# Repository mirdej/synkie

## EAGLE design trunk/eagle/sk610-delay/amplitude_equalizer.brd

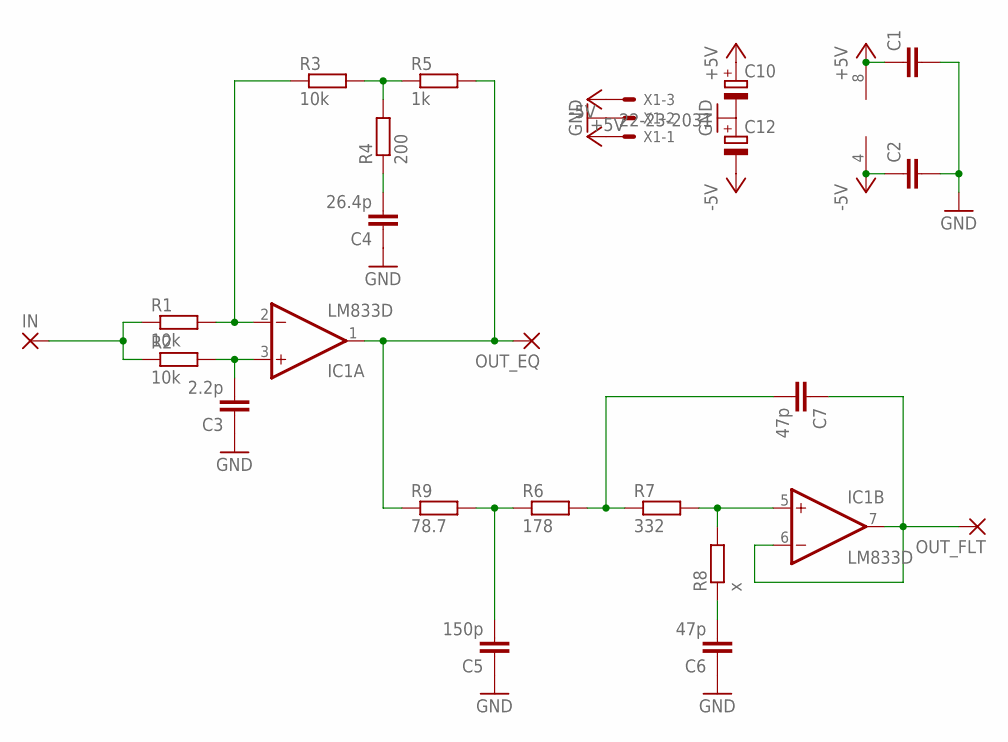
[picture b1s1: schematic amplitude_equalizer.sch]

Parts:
C1, C2: C-EUC1206; C1206
C3: 2.2p; C1206
C4: 26.4p; C1206
C5: 150p; C1206
C6, C7: 47p; C1206
C10, C12: CPOL-EUCT6032; CT6032
IC1: LM833D; SO08
IN: 3,17/1,1
OUT_EQ: 3,17/1,1
OUT_FLT: 3,17/1,1
R1, R2, R3: 10k; R1206
R4: 200; R1206
R5: 1k; R1206
R6: 178; R1206
R7: 332; R1206
R8: x; R1206
R9: 78.7; R1206
X1: 22-23-2031

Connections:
+5V: C1.1, C10.+, IC1.8 (V+), X1.3
-5V: C2.1, C12.-, IC1.4 (V-), X1.1
GND: C1.2, C2.2, C3.1, C4.1, C5.1, C6.1, C10.-, C12.+, X1.2
unnamed: IC1.2 (-IN), R1.2, R3.1
unnamed: C3.2, IC1.3 (+IN), R2.2
unnamed: IN.1, R1.1, R2.1
unnamed: IC1.1 (OUT), OUT_EQ.1, R5.2, R9.1
unnamed: C4.2, R4.1
unnamed: R3.2, R4.2, R5.1
unnamed: C5.2, R6.1, R9.2
unnamed: C7.2, R6.2, R7.1
unnamed: IC1.5 (+IN), R7.2, R8.2
unnamed: C6.2, R8.1
unnamed: C7.1, IC1.6 (-IN), IC1.7 (OUT), OUT_FLT.1

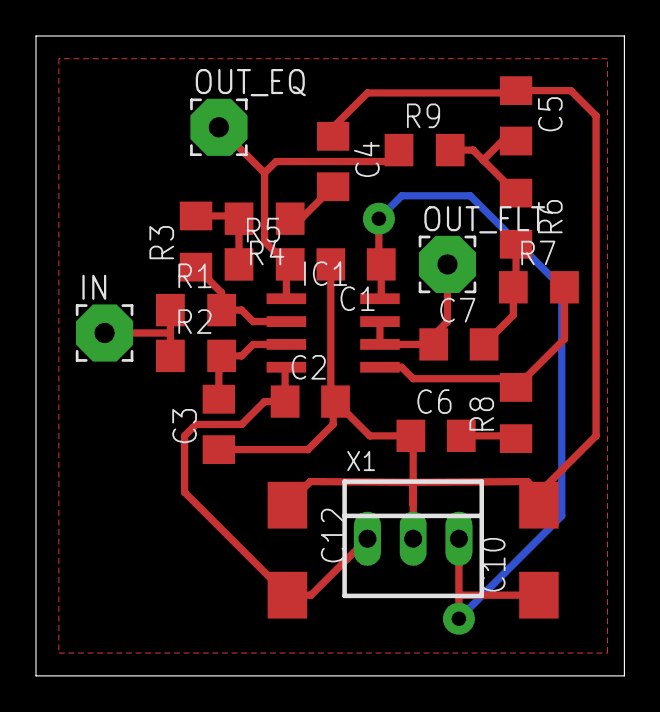
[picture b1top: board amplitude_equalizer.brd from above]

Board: 2 copper layers, 32.7 x 35.5 mm, 23 parts (0 on the bottom side), 14 nets.

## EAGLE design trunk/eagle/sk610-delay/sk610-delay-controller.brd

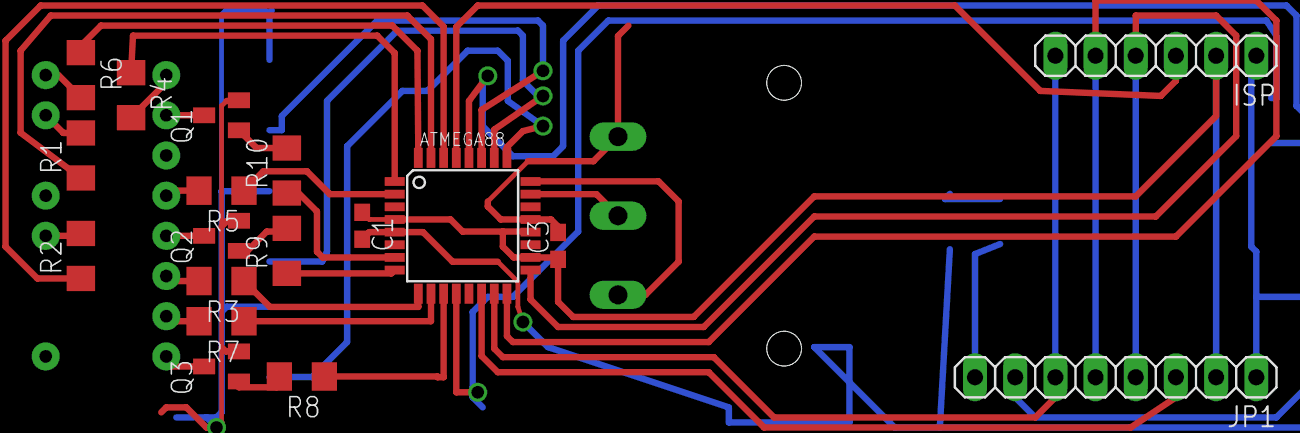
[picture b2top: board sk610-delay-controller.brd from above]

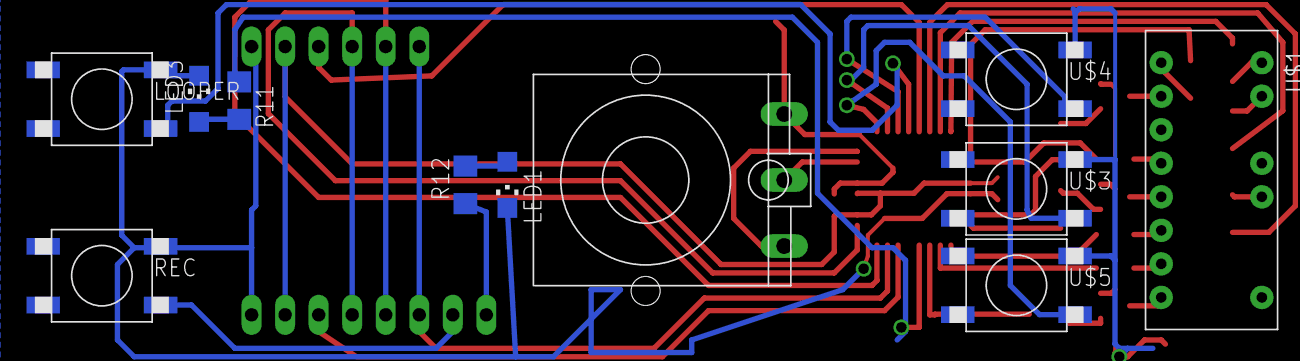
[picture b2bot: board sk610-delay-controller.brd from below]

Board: 2 copper layers, 29 parts (11 on the bottom side), 41 nets.

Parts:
ATMEGA88: ATMEGA88; TQFP32-08
C1, C3: C0603
ISP: 1X06
JP1: 1X08
LED1, LED3: CHIPLED_1206
LOOPER: PRINTTASTER_SMD; SMD_SWITCH
Q1, Q2, Q3: BC817-16LT1SMD; SOT23-BEC
R1, R2, R3, R4, R5, R6, R7, R8, R9, R10: R1206
R11, R12: 200; R1206
REC: PRINTTASTER_SMD; SMD_SWITCH
U$1: LTC-2721-7-SEGMENT; LTC-2721
U$2: STEC16B04
U$3, U$4, U$5: PRINTTASTER_SMD; SMD_SWITCH

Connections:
GND: ATMEGA88.5, ATMEGA88.21, C1.2, C3.2, ISP.1, JP1.1, LED1.C, LED3.C, LOOPER.AA, Q1.E, Q2.E, Q3.E, REC.AA, U$2.C, U$3.AA, U$4.AA, U$5.AA
unnamed: ATMEGA88.30, R2.1
unnamed: ATMEGA88.31, R1.1
unnamed: ATMEGA88.32, R6.1
unnamed: ATMEGA88.1, R4.1
unnamed: ATMEGA88.2, R5.1
unnamed: ATMEGA88.8, R9.1
unnamed: ATMEGA88.7, R10.1
unnamed: ATMEGA88.11, R8.1
unnamed: ATMEGA88.9, R3.1
unnamed: R1.2, U$1.P$12
unnamed: R2.2, U$1.P$10
unnamed: R3.2, U$1.P$6
unnamed: R4.2, U$1.P$1
unnamed: R5.2, U$1.P$4
unnamed: R6.2, U$1.P$13
unnamed: R7.2, U$1.P$7
unnamed: ATMEGA88.29, ISP.3
unnamed: ATMEGA88.17, ISP.4, JP1.4
unnamed: ATMEGA88.16, ISP.5, JP1.5
unnamed: ATMEGA88.15, ISP.6, JP1.6
unnamed: ATMEGA88.14, JP1.3
unnamed: ATMEGA88.10, R7.1
unnamed: ATMEGA88.23, U$2.B
unnamed: ATMEGA88.24, U$2.A
unnamed: Q1.B, R10.2
unnamed: Q2.B, R9.2
unnamed: Q3.B, R8.2
unnamed: Q1.C, U$1.P$2
unnamed: Q2.C, U$1.P$5
unnamed: Q3.C, U$1.P$8
unnamed: ATMEGA88.25, U$5.BB
unnamed: ATMEGA88.26, U$3.BB
unnamed: ATMEGA88.27, U$4.BB
unnamed: JP1.7, REC.BB
unnamed: ATMEGA88.28, LOOPER.BB
unnamed: ATMEGA88.12, R11.1
unnamed: LED1.A, R12.2
unnamed: JP1.8, R12.1
unnamed: LED3.A, R11.2
VCC: ATMEGA88.4, ATMEGA88.18, ATMEGA88.20, C1.1, C3.1, ISP.2, JP1.2

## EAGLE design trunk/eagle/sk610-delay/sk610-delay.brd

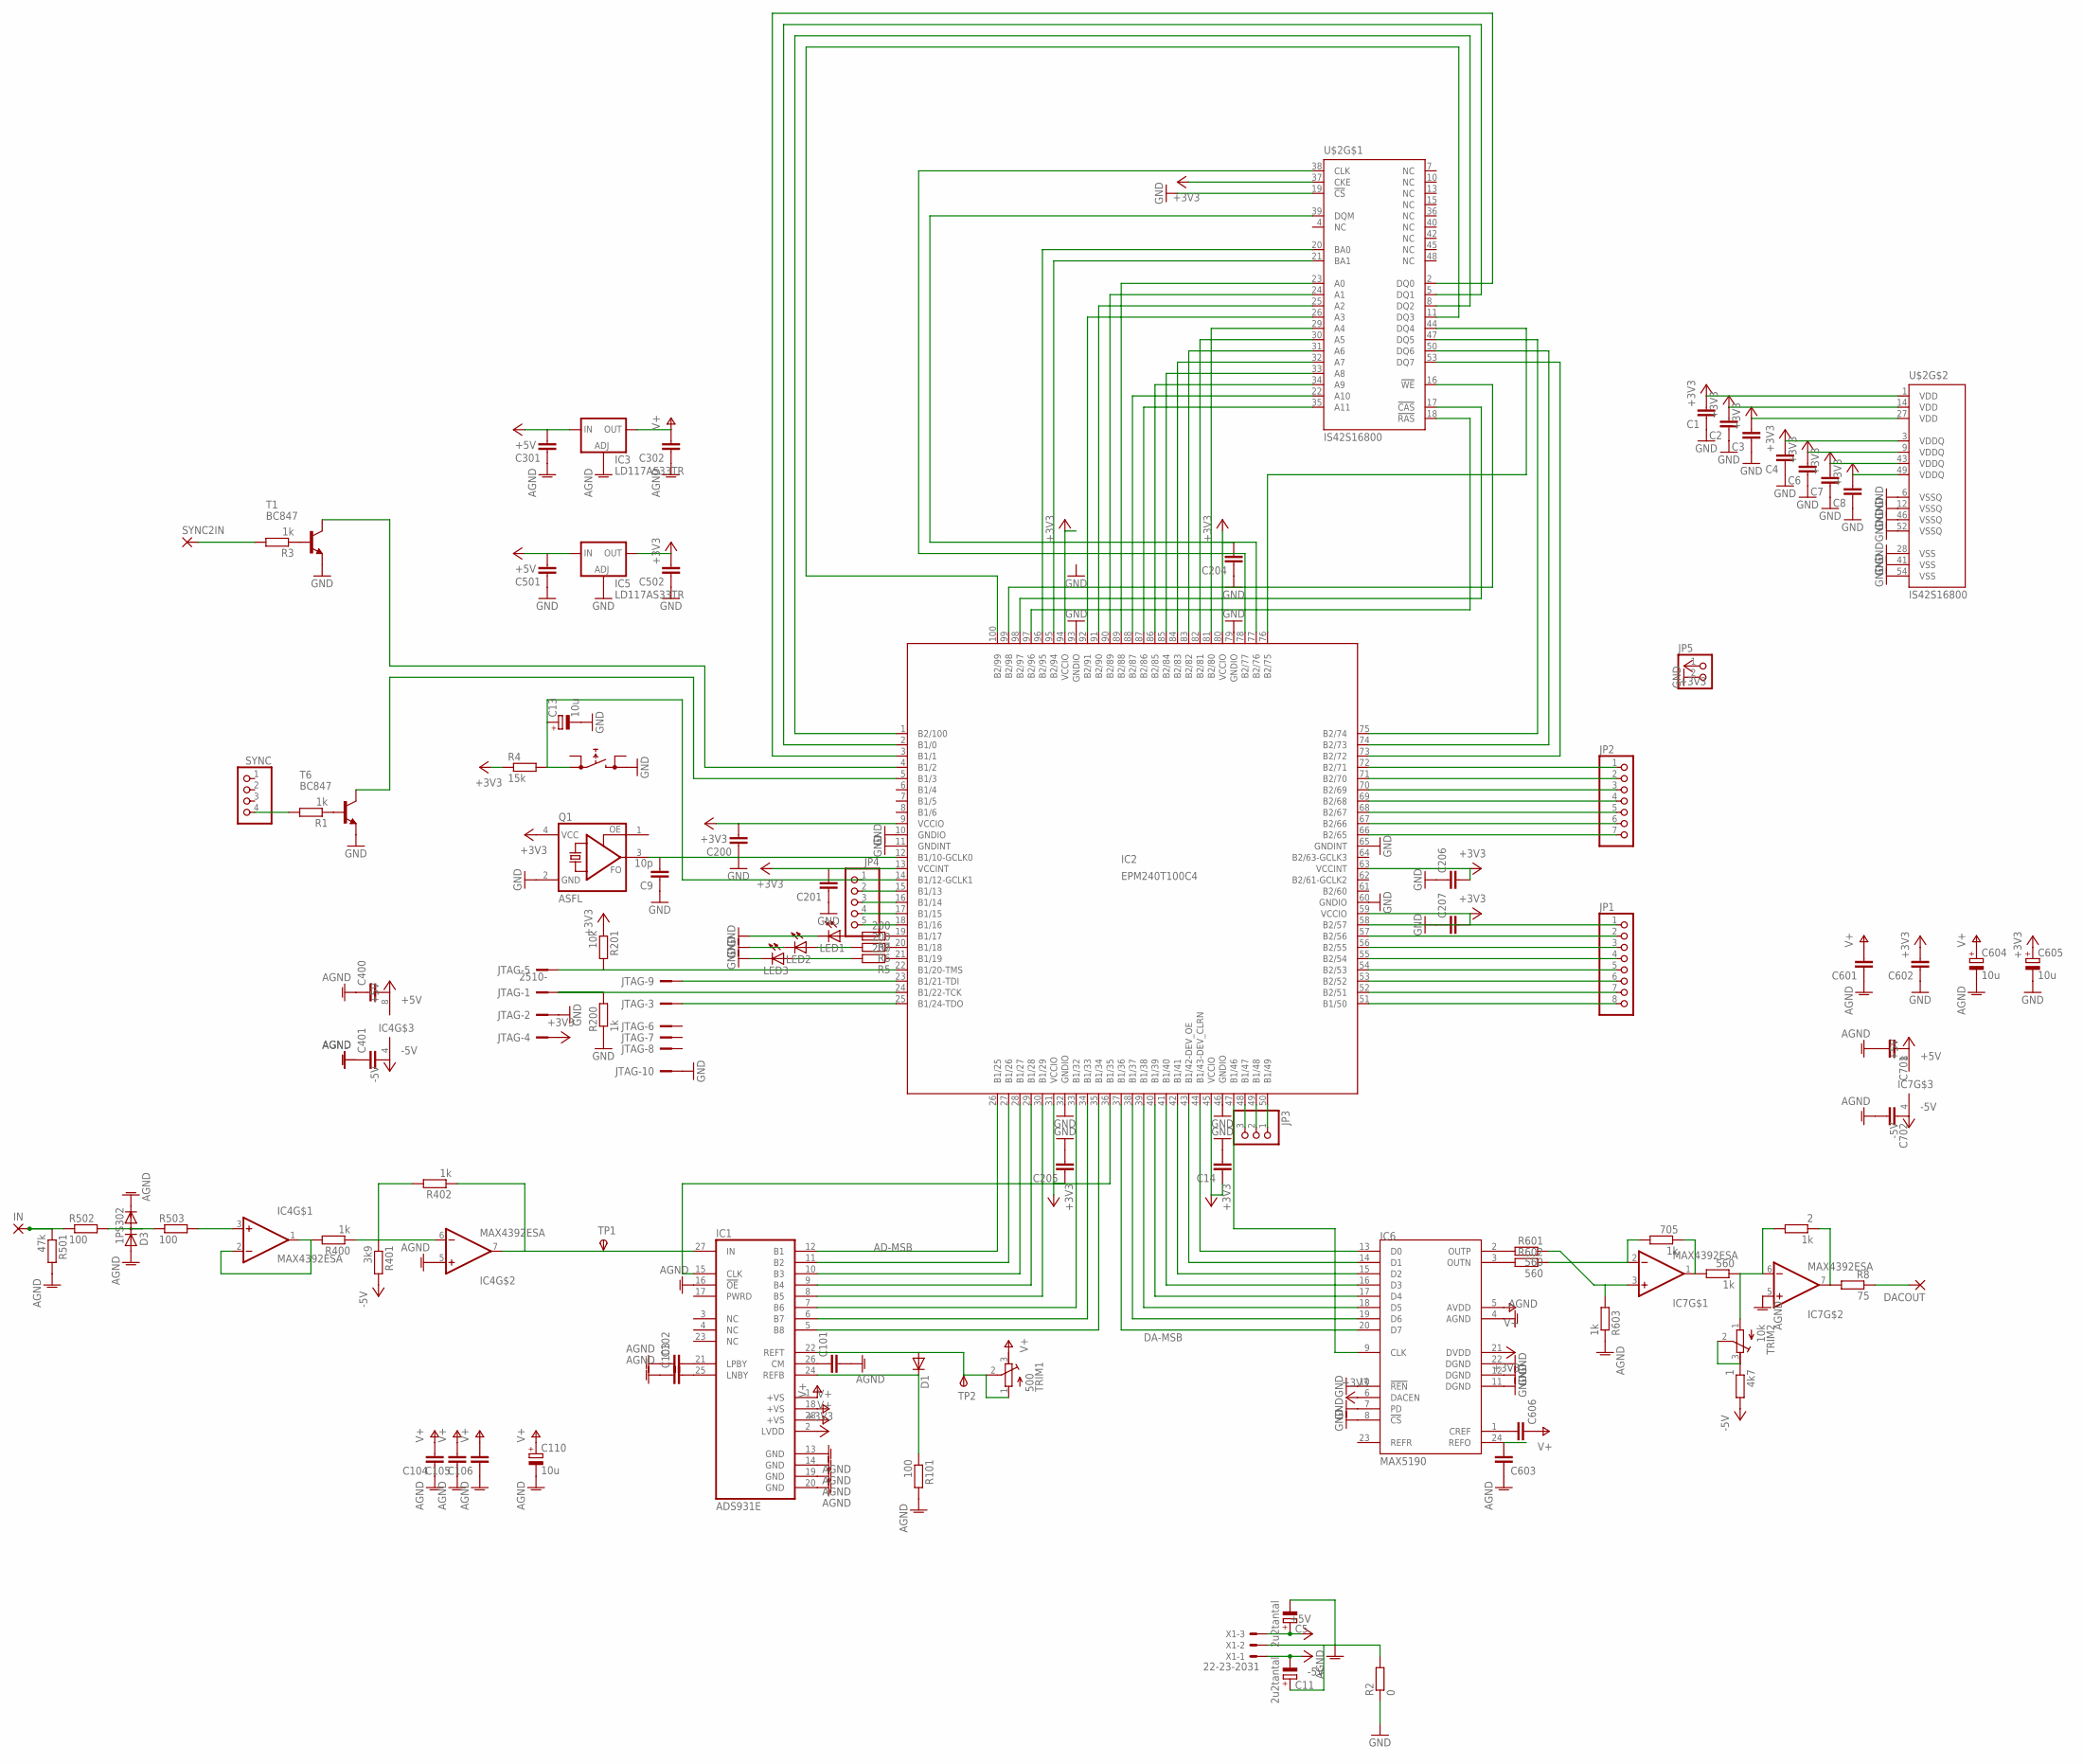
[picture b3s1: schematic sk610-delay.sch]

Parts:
1: 4k7; R1206
2, 560, 705: 1k; R1206
C1, C2, C3, C4, C6, C7, C8, C14, C101, C102, C103, C104, C106, C200, C201, C204, C205, C206, C207, C301, C302, C400, C401, C501, C502, C601, C602, C603, C606, C701, C702: C-EUC0603; C0603
C5, C11: 2u2tantal; CT3528
C9: 10p; C0603
C13, C110, C604, C605: 10u; SMC_B
C105: C-EUC1206; C1206
D1: DIODE-MINIMELF; MINIMELF
D3: 1PS302; SOT23
DACOUT: 3,17/1,1
IC1: ADS931E; SSOP28BU
IC2: EPM240T100C4; TQFP100
IC3, IC5: LD117AS33TR; SOT223
IC4, IC7: MAX4392ESA; SO08
IC6: MAX5190; QSOP24
IN: 3,17/1,1
JP1: PINHD-1X8; 1X08
JP2: PINHD-1X7; 1X07
JP3: PINHD-1X3; 1X03
JP4: PINHD-1X5; 1X05
JP5: PINHD-1X2; 1X02
JTAG: 2510-; PAK100/2500-10
LED1, LED2, LED3: LEDCHIPLED_1206; CHIPLED_1206
Q1: ASFL; ASF
R1, R3, R200, R400, R402, R603: 1k; R1206
R2: 0; R1206
R4: 15k; R0805
R5, R6, R7: 200; R1206
R8: 75; R1206
R101, R502, R503: 100; R1206
R201: 10k; R1206
R401: 3k9; R1206
R501: 47k; R1206
R601, R602: 560; R1206
SYNC: PINHD-1X4; 1X04
SYNC2IN: 3,17/1,1
T1, T6: BC847; SOT23
TP1, TP2: TPSPAD1-13; P1-13
TRIM1: 500; RTRIM64Y
TRIM2: 10k; RTRIM64Y
U$2: IS42S16800; TSOP54-400
U$4: PRINTTASTER_SMD; SMD_SWITCH
X1: 22-23-2031

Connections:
+3V3: C1.2, C2.2, C3.2, C4.2, C6.2, C7.2, C8.2, C14.1, C200.2, C201.2, C204.2, C205.1, C206.2, C207.2, C502.2, C602.2, C605.+, IC1.2 (LVDD), IC2.9 (VCCIO), IC2.13 (VCCINT), IC2.31 (VCCIO), IC2.45 (VCCIO), IC2.59 (VCCIO), IC2.63 (VCCINT), IC2.80 (VCCIO), IC2.94 (VCCIO), IC5.4 (OUT), IC6.6 (DACEN), IC6.21 (DVDD), JP5.1, JTAG.4, Q1.4 (VCC), R4.1, R201.1, U$2.1 (VDD), U$2.3 (VDDQ), U$2.9 (VDDQ), U$2.14 (VDD), U$2.27 (VDD), U$2.37 (CKE), U$2.43 (VDDQ), U$2.49 (VDDQ)
+5V: C5.+, C301.2, C400.2, C501.2, C701.1, IC3.3 (IN), IC4.8 (+5V), IC5.3 (IN), IC7.8 (+5V), X1.3
-5V: 1.2, C11.-, C401.2, C702.1, IC4.4 (-5V), IC7.4 (-5V), R401.2, X1.1
AD-MSB: IC1.12 (B1), IC2.26 (B1/25)
ADCLK: IC1.15 (CLK), IC2.36 (B1/35)
AGND: C5.-, C11.+, C101.2, C102.1, C103.1, C104.1, C105.1, C106.1, C110.-, C301.1, C302.1, C400.1, C401.1, C601.1, C603.1, C604.-, C701.2, C702.2, D3.1 (A), D3.2 (C), IC1.13 (GND), IC1.14 (GND), IC1.16 (!OE), IC1.19 (GND), IC1.20 (GND), IC3.1 (ADJ), IC4.5 (+IN), IC6.4 (AGND), IC7.5 (+IN), R2.2, R101.2, R501.2, R603.1, X1.2
BUTTON: IC2.68 (B2/67), JP2.5
DA-MSB: IC2.37 (B1/36), IC6.20 (D7)
DACLK: IC2.47 (B1/46), IC6.9 (CLK)
GND: C1.1, C2.1, C3.1, C4.1, C6.1, C7.1, C8.1, C9.1, C13.-, C14.2, C200.1, C201.1, C204.1, C205.2, C206.1, C207.1, C501.1, C502.1, C602.1, C605.-, IC2.10 (GNDIO), IC2.11 (GNDINT), IC2.32 (GNDIO), IC2.46 (GNDIO), IC2.60 (GNDIO), IC2.65 (GNDINT), IC2.79 (GNDIO), IC2.93 (GNDIO), IC5.1 (ADJ), IC6.7 (PD), IC6.8 (!CS), IC6.10 (!REN), IC6.11 (DGND), IC6.12 (DGND), IC6.22 (DGND), JP5.2, JTAG.2, JTAG.10, LED1.C, LED2.C, LED3.C, Q1.2 (GND), R2.1, R200.1, T1.2 (E), T6.2 (E), U$2.6 (VSSQ), U$2.12 (VSSQ), U$2.19 (!CS), U$2.28 (VSS), U$2.41 (VSS), U$2.46 (VSSQ), U$2.52 (VSSQ), U$2.54 (VSS), U$4.BB (1)
LED: IC2.67 (B2/66), JP2.6
MISO: IC2.70 (B2/69), JP2.3
MOSI: IC2.69 (B2/68), JP2.4
N: IC2.58 (B2/57), JP1.1
unnamed: IC2.21 (B1/19), R5.1
unnamed: IC2.25 (B1/24-TDO), JTAG.3
unnamed: IC2.23 (B1/21-TDI), JTAG.9
unnamed: C9.2, IC2.12 (B1/10-GCLK0), Q1.3 (FO)
unnamed: IC2.92 (B2/91), U$2.26 (A3)
unnamed: IC2.91 (B2/90), U$2.25 (A2)
unnamed: IC2.90 (B2/89), U$2.24 (A1)
unnamed: IC2.89 (B2/88), U$2.23 (A0)
unnamed: IC2.100 (B2/99), U$2.11 (DQ3)
unnamed: IC1.11 (B2), IC2.27 (B1/26)
unnamed: IC1.10 (B3), IC2.28 (B1/27)
unnamed: IC2.76 (B2/75), U$2.44 (DQ4)
unnamed: IC2.88 (B2/87), U$2.22 (A10)
unnamed: IC2.87 (B2/86), U$2.35 (A11)
unnamed: IC2.86 (B2/85), U$2.34 (A9)
unnamed: IC2.85 (B2/84), U$2.33 (A8)
unnamed: IC2.84 (B2/83), U$2.32 (A7)
unnamed: IC2.83 (B2/82), U$2.31 (A6)
unnamed: IC2.82 (B2/81), U$2.30 (A5)
unnamed: C603.2, IC6.24 (REFO)
unnamed: C606.2, IC6.1 (CREF)
unnamed: IC6.2 (OUTP), R601.2
unnamed: IC6.3 (OUTN), R602.2
unnamed: IC7.3 (+IN), R601.1, R603.2
unnamed: 705.2, IC7.2 (-IN), R602.1
unnamed: 560.2, 705.1, IC7.1 (OUT)
unnamed: 2.2, 560.1, IC7.6 (-IN), TRIM2.1 (E)
unnamed: IC2.81 (B2/80), U$2.29 (A4)
unnamed: IC2.95 (B2/94), U$2.21 (BA1)
unnamed: IC2.1 (B2/100), U$2.8 (DQ2)
unnamed: IC2.96 (B2/95), U$2.20 (BA0)
unnamed: IC2.78 (B2/77), U$2.38 (CLK)
unnamed: D1.C, IC1.24 (REFB), R101.1
unnamed: IC2.77 (B2/76), U$2.39 (DQM)
unnamed: IC2.2 (B1/0), U$2.5 (DQ1)
unnamed: IC2.3 (B1/1), U$2.2 (DQ0)
unnamed: IC2.97 (B2/96), U$2.18 (!RAS)
unnamed: IC2.98 (B2/97), U$2.17 (!CAS)
unnamed: IC1.9 (B4), IC2.29 (B1/28)
unnamed: IC1.8 (B5), IC2.30 (B1/29)
unnamed: IC1.7 (B6), IC2.33 (B1/32)
unnamed: IC1.6 (B7), IC2.34 (B1/33)
unnamed: IC1.5 (B8), IC2.35 (B1/34)
unnamed: IC2.99 (B2/98), U$2.16 (!WE)
unnamed: IC2.75 (B2/74), U$2.47 (DQ5)
unnamed: IC2.38 (B1/37), IC6.19 (D6)
unnamed: IC2.39 (B1/38), IC6.18 (D5)
unnamed: IC2.40 (B1/39), IC6.17 (D4)
unnamed: IC2.41 (B1/40), IC6.16 (D3)
unnamed: IC2.42 (B1/41), IC6.15 (D2)
unnamed: IC2.43 (B1/42-DEV_OE), IC6.14 (D1)
unnamed: IC2.44 (B1/43-DEV_CLRN), IC6.13 (D0)
unnamed: IC2.74 (B2/73), U$2.50 (DQ6)
unnamed: IC2.73 (B2/72), U$2.53 (DQ7)
unnamed: 2.1, IC7.7 (OUT), R8.2
unnamed: C102.2, IC1.21 (LPBY)
unnamed: C103.2, IC1.25 (LNBY)
unnamed: IC4.3 (+IN), R503.2
unnamed: C101.1, IC1.26 (CM)
unnamed: D1.A, IC1.22 (REFT), TP2.TP, TRIM1.1 (E), TRIM1.2 (S)
unnamed: IC2.19 (B1/17), R7.1
unnamed: LED1.A, R7.2
unnamed: IC2.20 (B1/18), R6.1
unnamed: LED2.A, R6.2
unnamed: LED3.A, R5.2
unnamed: DACOUT.1, R8.1
unnamed: IC2.54 (B2/53), JP1.5
unnamed: IC2.53 (B2/52), JP1.6
unnamed: IC2.52 (B2/51), JP1.7
unnamed: IN.1, R501.1, R502.1
unnamed: D3.3 (AC), R502.2, R503.1
unnamed: IC2.50 (B1/49), JP3.1
unnamed: IC2.49 (B1/48), JP3.2
unnamed: IC2.48 (B1/47), JP3.3
unnamed: IC2.15 (B1/13), JP4.2
unnamed: IC2.16 (B1/14), JP4.3
unnamed: IC2.17 (B1/15), JP4.4
unnamed: IC4.1 (OUT), IC4.2 (-IN), R400.2
unnamed: IC4.6 (-IN), R400.1, R401.1, R402.2
unnamed: IC1.27 (IN), IC4.7 (OUT), R402.1, TP1.TP
unnamed: R1.1, T6.1 (B)
unnamed: 1.1, TRIM2.2 (S), TRIM2.3 (A)
unnamed: R1.2, SYNC.4
unnamed: IC2.4 (B1/2), T1.3 (C)
unnamed: R3.1, T1.1 (B)
unnamed: R3.2, SYNC2IN.1
NN: IC2.57 (B2/56), JP1.2
NNN: IC2.56 (B2/55), JP1.3
NNNN: IC2.55 (B2/54), JP1.4
P51: IC2.51 (B1/50), JP1.8
REC: IC2.66 (B2/65), JP2.7
RESET: C13.+, IC2.14 (B1/12-GCLK1), JP4.1, R4.2, U$4.AA (0)
SCK: IC2.71 (B2/70), JP2.2
SS: IC2.72 (B2/71), JP2.1
SWITCH: IC2.18 (B1/16), JP4.5
TCK: IC2.24 (B1/22-TCK), JTAG.1, R200.2
TMS: IC2.22 (B1/20-TMS), JTAG.5, R201.2
V+: C104.2, C105.2, C106.2, C110.+, C302.2, C601.2, C604.+, C606.1, IC1.1 (+VS), IC1.18 (+VS), IC1.28 (+VS), IC3.4 (OUT), IC6.5 (AVDD), TRIM1.3 (A)
VSYNC: IC2.5 (B1/3), T6.3 (C)

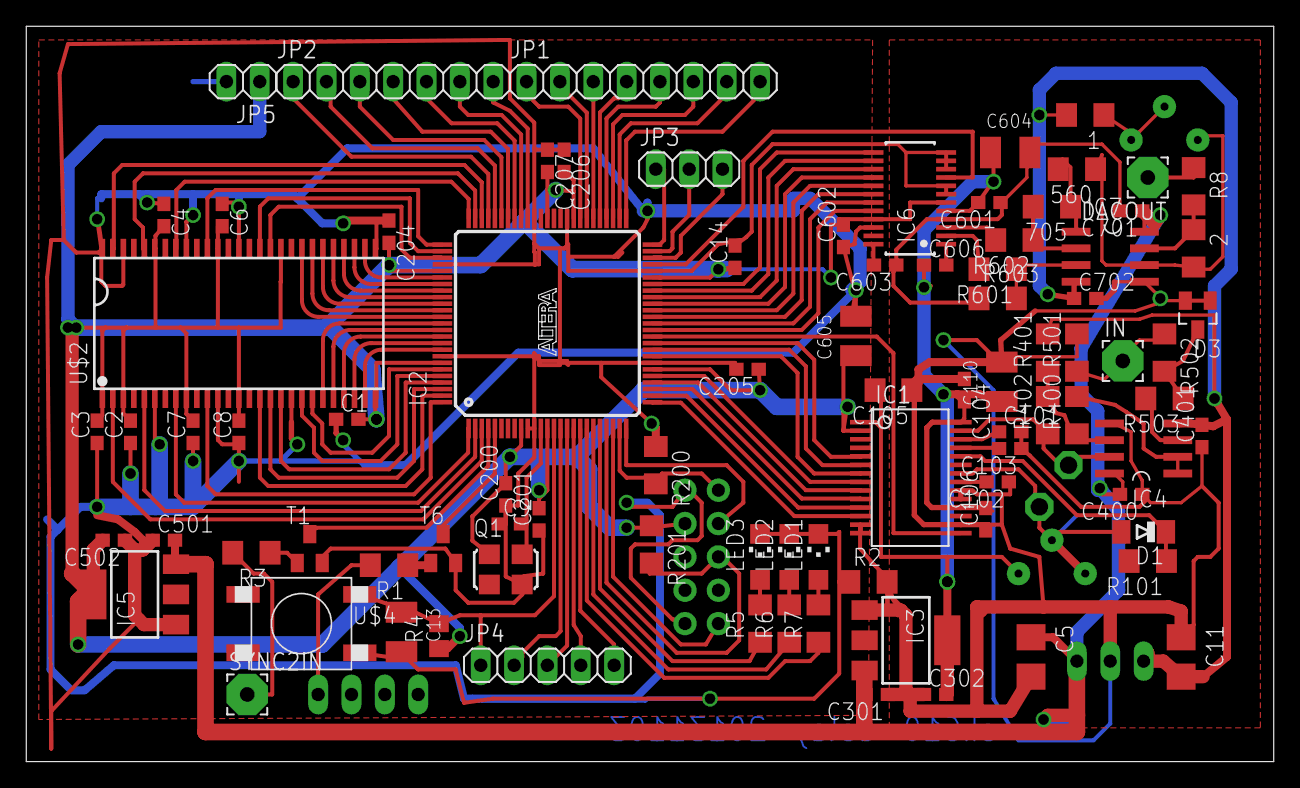
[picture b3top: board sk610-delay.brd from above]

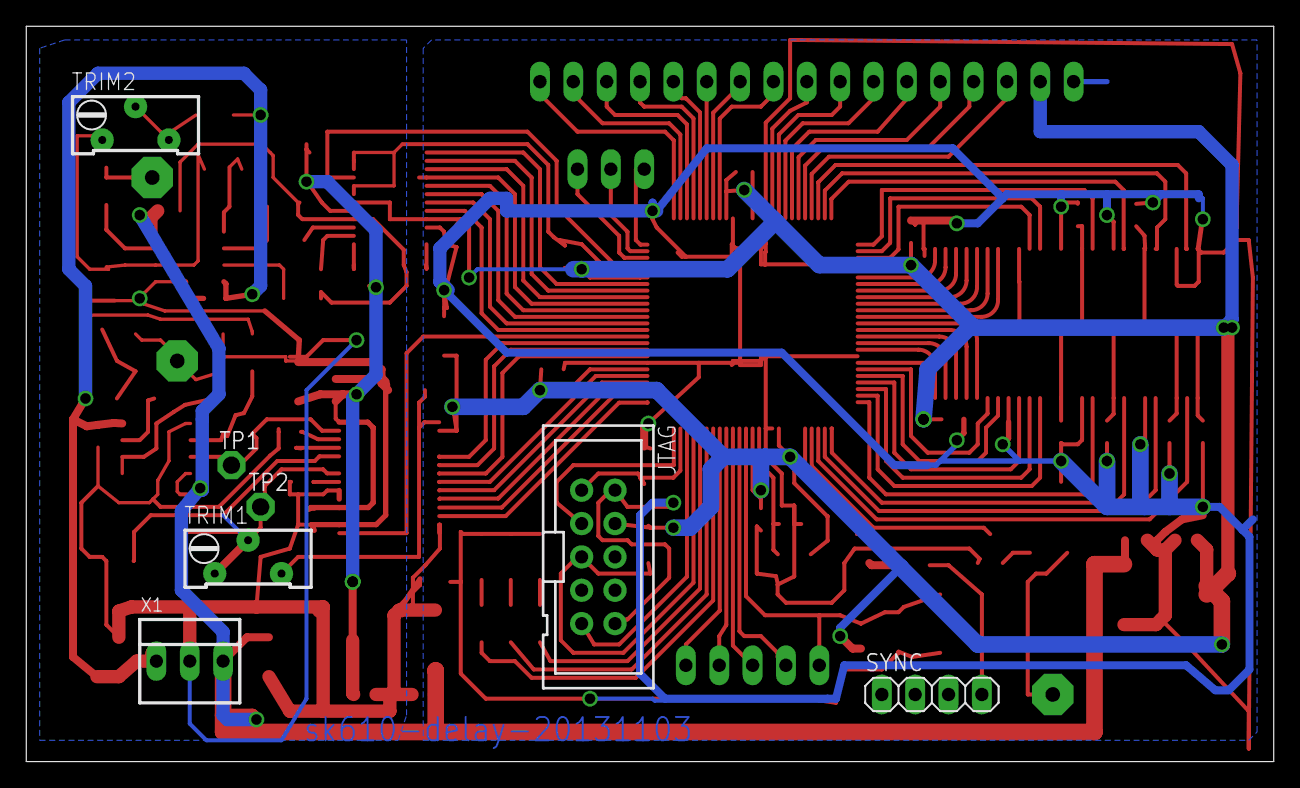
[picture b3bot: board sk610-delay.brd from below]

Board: 2 copper layers, 95.0 x 56.0 mm, 95 parts (7 on the bottom side), 113 nets.
